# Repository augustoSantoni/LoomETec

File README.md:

# 🧶 LOOM ETEC - Telar Automático con Sistema Jacquard

## 📖 Descripción del Proyecto

El proyecto **LOOM ETEC** se desarrolla en el marco del taller **AeroGlobETec**, que combina disciplinas como ciencias, electrónica, informática, mecánica y dibujo técnico.

### 🎯 Motivación

Este proyecto nace de una motivación personal, inspirada en la memoria de mi abuela, quien dedicó gran parte de su vida a tejer y donar sus creaciones a quienes más lo necesitaban. Tras su fallecimiento, surgió la idea de conmemorar su legado mediante la creación de un telar automático que perpetúe su espíritu altruista e integre conocimientos técnicos.

**Objetivo principal**: Automatizar el proceso de tejido para producir mantas destinadas a instituciones que asisten a recién nacidos en situación de vulnerabilidad.

### 🏗️ Tipos de Telares Implementados

#### 1️⃣ Telar Convencional

Compuesto por cuatro partes esenciales:

- **Caladores**: Varillas que levantan o bajan selectivamente los hilos de la urdimbre, creando una abertura (llamada "calada") por donde pasa la lanzadera con el hilo de la trama.
- **Peine**: Herramienta dentada que presiona y compacta el hilo de la trama después de cada pasada de la lanzadera.
- **Lanzadera**: Dispositivo que transporta el hilo de la trama a través de los hilos de la urdimbre para tejer la tela.
- **Plegador**: Mecanismo que enrolla la tela tejida, manteniendo la tensión y avanzando la urdimbre a medida que se teje.

#### 2️⃣ Telar Jacquard (31 columnas)

Una reversión del telar de Jacquard, máquina textil que utiliza patrones digitales (en lugar de tarjetas perforadas) para controlar automáticamente el levantamiento individual de hilos de urdimbre, permitiendo la creación de patrones complejos.

**Sistema de control**:
- **Eje X**: Motor PAP para movimiento horizontal (31 posiciones)
- **Eje Z**: Servomotor para selección arriba/abajo de cada hilo
- **Eje Y**: Motor DC para elevación del cabezal (calada)

---

## 🛠️ Tecnologías Utilizadas

### Software

#### **PlatformIO**
IDE profesional para desarrollo de sistemas embebidos. Proporciona gestión de bibliotecas, compilación cruzada y soporte para múltiples plataformas de hardware. Utilizado para programar el ESP32 con C++.

#### **Node-RED**
Herramienta de programación visual basada en flujos para conectar dispositivos IoT. Actúa como middleware entre la interfaz web y el broker MQTT, procesando las peticiones HTTP y transformándolas en comandos MQTT.

#### **MQTT (Mosquitto/HiveMQ Cloud)**
Protocolo de mensajería ligero para IoT. Permite la comunicación asíncrona entre el ESP32 y el servidor mediante topics (tópicos). Se puede usar Mosquitto localmente o HiveMQ Cloud para acceso remoto.

#### **Autodesk Fusion 360**
Software de modelado 3D CAD/CAM utilizado para diseñar las piezas mecánicas del telar, incluyendo soportes, engranajes y estructuras.

#### **Python 3.x + Tkinter**
Lenguaje de programación utilizado para desarrollar el **Editor de Trama**, una aplicación de escritorio que permite crear patrones de tejido de forma visual mediante una interfaz gráfica.

### Hardware

| Componente | Descripción | Cantidad |
|------------|-------------|----------|
| **ESP32 DevKit V1** | Microcontrolador principal con WiFi y Bluetooth integrado | 1 |
| **Motores DC** | Para lanzadera, peine y eje Y (elevación) | 3-4 |
| **Servomotores** | Para selección de hilos (Eje Z) en sistema Jacquard | 1 |
| **Motores PAP + DVR8825** | Motor paso a paso con driver para eje X (horizontal) y plegador | 2 |
| **Puente H L298N** | Controlador para motores DC bidireccionales | 2-3 |
| **Sensores Fin de Carrera** | Detección de posiciones límite (mínimo 7) | 7+ |
| **Fuente de Alimentación** | 12V 5A para motores | 1 |
| **Cables y Conectores** | Jumpers, borneras, conectores Dupont | Varios |

---

## 📋 Requisitos Previos

### Software a Instalar

1. **Visual Studio Code** con extensión **PlatformIO IDE**
2. **Node.js** (v14 o superior) para Node-RED
3. **Python 3.8+** para el Editor de Trama
4. **Mosquitto MQTT Broker** (opcional, para pruebas locales)

---

## 🚀 Guía de Instalación

### 1. Instalación de PlatformIO

1. Descargar e instalar [Visual Studio Code](https://code.visualstudio.com/)
2. Abrir VS Code y dirigirse a **Extensions** (Ctrl+Shift+X)
3. Buscar **PlatformIO IDE** e instalar
4. Reiniciar VS Code
5. Verificar instalación: debería aparecer un ícono de hormiga en la barra lateral

### 2. Instalación de Node-RED

```bash
# Instalar Node.js desde https://nodejs.org/

# Instalar Node-RED globalmente
npm install -g node-red

# Instalar nodos adicionales necesarios
cd ~/.node-red
npm install node-red-dashboard
npm install node-red-contrib-mqtt-broker

# Iniciar Node-RED
node-red

# Acceder a http://localhost:1880
```

### 3. Instalación de Python y Dependencias

```bash
# Verificar instalación de Python
python --version

# Instalar dependencias del Editor de Trama
pip install pillow
pip install tk

# En Linux/Mac, puede ser necesario instalar tkinter:
sudo apt-get install python3-tk  # Ubuntu/Debian
```

### 4. Configuración de MQTT Broker

#### Opción A: Mosquitto Local

```bash
# Windows: Descargar desde https://mosquitto.org/download/
# Linux:
sudo apt-get install mosquitto mosquitto-clients

# Iniciar servicio
sudo systemctl start mosquitto
sudo systemctl enable mosquitto

# Verificar que está corriendo en puerto 1883
netstat -tuln | grep 1883
```

#### Opción B: HiveMQ Cloud (Recomendado para acceso remoto)

1. Crear cuenta gratuita en [HiveMQ Cloud](https://www.hivemq.com/mqtt-cloud-broker/)
2. Crear un nuevo cluster
3. Anotar credenciales (URL, puerto, usuario, contraseña)
4. Actualizar configuración en `main.cpp` y flujos de Node-RED

---

## 🎨 Editor de Trama - Guía de Uso

### Iniciar el Editor

```bash
python Editor-Trama.py
```

### Funcionalidades Principales

#### 1. Crear un Patrón

- **Tamaño**: El editor trabaja con una cuadrícula de 24x24 píxeles por defecto
- **Colores**: 
  - Negro (patrón activo)
  - Blanco (fondo)
- **Pintar**: Click izquierdo para pintar, click derecho para borrar

#### 2. Pinceles Disponibles

| Pincel | Descripción |
|--------|-------------|
| Punto | Pinta un solo píxel |
| Línea H | Línea horizontal de 3 píxeles |
| Línea V | Línea vertical de 3 píxeles |
| Cruz | Forma de cruz (5 píxeles) |
| Cuadrado | Cuadrado de 2x2 |
| Diagonal | Diagonal de 3x3 |

**Crear pincel personalizado**:
1. Click en "Crear Pincel"
2. Definir dimensiones (ej: 3x3)
3. Click en "Generar Cuadrícula"
4. Pintar el patrón deseado
5. "Guardar Pincel" → ingresar nombre → guardar archivo `.brush`

#### 3. Ajustar Tamaño del Lienzo

- **Agrandar**: Ctrl/Cmd + `+` o botón "Agrandar" (incrementa 4 filas)
- **Achicar**: Ctrl/Cmd + `-` o botón "Achicar" (reduce 4 filas, mínimo 24)

#### 4. Replicar Diseño

1. Crear un patrón base en las primeras 24 filas
2. Ingresar número de repeticiones (ej: 3)
3. Click en "Aplicar Replicación"
4. El patrón se repetirá verticalmente

#### 5. Exportar Patrón

##### Guardar como PNG (Ctrl/Cmd + S)
- Genera imagen con franjas de sincronización (patrón ajedrezado)
- Formato: 1 píxel = 1 hilo
- Incluye franjas cada 4 filas/columnas para alineación

##### Guardar como JSON (Ctrl/Cmd + J)
```json
{
  "dimensiones": [31, 100],
  "datos": [
    [0, 1, 0, 1, ...],
    [1, 0, 1, 0, ...],
    ...
  ]
}
```
- **IMPORTANTE**: Para el telar Jacquard, el patrón debe tener exactamente **31 columnas**
- 0 = hilo abajo (blanco), 1 = hilo arriba (negro)

#### 6. Atajos de Teclado

| Atajo | Acción |
|-------|--------|
| Ctrl/Cmd + Z | Deshacer |
| Ctrl/Cmd + Y | Rehacer |
| Ctrl/Cmd + L | Limpiar lienzo |
| Ctrl/Cmd + S | Guardar PNG |
| Ctrl/Cmd + J | Guardar JSON |
| Ctrl/Cmd + `+` | Agrandar lienzo |
| Ctrl/Cmd + `-` | Achicar lienzo |

---

## ⚡ Puesta en Marcha del Telar

### Paso 1: Conexiones del ESP32

#### Telar Convencional

```
LANZADERA:
  enaLanzadera → GPIO 29 (PWM)
  lanzadera1 → GPIO 28 (dirección 1)
  lanzadera2 → GPIO 20 (dirección 2)
  fdcLanzadera1 → GPIO 40 (fin de carrera izq)
  fdcLanzadera2 → GPIO 15 (fin de carrera der)

CALADORES:
  enaCaladores → GPIO 34 (PWM)
  caladores1 → GPIO 35 (subir)
  caladores2 → GPIO 27 (bajar)
  fdcCaladores → GPIO 16 (fin de carrera)

PEINE:
  enaPeine → GPIO 22 (PWM)
  peine1 → GPIO 24 (adelante)
  peine2 → GPIO 23 (atrás)
  fdcPeine1 → GPIO 13 (fin de carrera adelante)
  fdcPeine2 → GPIO 14 (fin de carrera atrás)

PLEGADOR:
  stepPlegador → GPIO 8 (pulsos)
  dirPlegador → GPIO 18 (dirección)
```

#### Telar Jacquard (adicional al convencional)

```
EJE X (Motor PAP):
  stepEjeX → GPIO 25
  dirEjeX → GPIO 26
  fdcEjeX_Home → GPIO 17 (posición inicial)

EJE Z (Servo):
  servoEjeZ → GPIO 19

EJE Y (Motor DC elevación):
  enaEjeY → GPIO 34 (PWM)
  ejeY_Up → GPIO 35
  ejeY_Down → GPIO 27
  fdcEjeY_Arriba → GPIO 16
  fdcEjeY_Abajo → GPIO 21
```

#### Diagrama de Conexión Puente H (ejemplo L298N)

```
ESP32           L298N          Motor DC
GPIO XX   →     ENA      →     (PWM control velocidad)
GPIO YY   →     IN1      →     (dirección)
GPIO ZZ   →     IN2      →     (dirección)
              OUT1/OUT2  →     Motor
GND       →     GND
12V       →     12V (fuente externa)
```

#### Conexión DVR8825 (Motor PAP)

```
ESP32           DVR8825        Motor PAP
GPIO XX   →     STEP
GPIO YY   →     DIR
             →  ENABLE (a GND o control)
12V fuente →    VMOT
GND        →    GND
             →  A1, A2, B1, B2 → Bobinas del motor
```

### Paso 2: Programar el ESP32

```bash
# Clonar el repositorio
git clone https://github.com/tu-usuario/loom-etec.git
cd loom-etec

# Abrir el proyecto en VS Code con PlatformIO
code .

# Configurar WiFi y MQTT en main.cpp (líneas 50-54)
String ssid = "TU_WIFI";
String password = "TU_PASSWORD";
const char* mqtt_server = "TU_BROKER_IP";  # localhost o IP de HiveMQ
const char* mqtt_user = "usuario";
const char* mqtt_pass = "contraseña";

# Compilar y subir (en VS Code)
# Click en el ícono "→" (PlatformIO: Upload) en la barra inferior
# O usar el atajo: Ctrl+Alt+U

# Monitorear salida serial
# Click en el ícono de enchufe (PlatformIO: Serial Monitor)
# O atajo: Ctrl+Alt+S
```

### Paso 3: Configurar Node-RED

```bash
# Iniciar Node-RED
node-red

# Abrir navegador en http://localhost:1880
```

#### Importar Flujo

1. Click en menú hamburguesa (☰) → **Import**
2. Seleccionar archivo:
   - `node-red-flujo-telar.json` (telar Jacquard con carga de patrón)
   - O `node-red-flujo-telar-simple.json` (telar convencional)
3. Click en **Import**

#### Configurar Broker MQTT en Node-RED

1. Doble click en cualquier nodo MQTT (ej: "mqtt_empezar")
2. Click en el lápiz junto a "Server"
3. Configurar:
   ```
   Server: localhost  (o IP del broker)
   Port: 1883
   Username: tu_usuario
   Password: tu_contraseña
   ```
4. Click en **Update** → **Done**
5. Click en **Deploy** (botón rojo arriba a la derecha)

#### Verificar Endpoints HTTP

Una vez desplegado, los siguientes endpoints estarán disponibles:

```
POST http://localhost:1880/api/empezar       - Iniciar tejido
POST http://localhost:1880/api/parar         - Detener tejido
POST http://localhost:1880/api/config/red    - Configurar WiFi
POST http://localhost:1880/api/config/patron - Cargar patrón JSON (solo Jacquard)
GET  http://localhost:1880/api/vueltas       - Obtener contador de vueltas
```

### Paso 4: Interfaz Web

#### Opción 1: Servidor Local Simple

```bash
# Navegar a la carpeta del proyecto
cd loom-etec

# Iniciar servidor HTTP simple con Python
python -m http.server 8000

# Abrir navegador en:
http://localhost:8000/index.html
```

#### Opción 2: Servidor Web Externo

Subir el archivo `index.html` a cualquier hosting web o usar:

```bash
# Con Node.js (live-server)
npm install -g live-server
live-server --port=8000
```

### Paso 5: Operación del Sistema

#### Para Telar Convencional

1. Verificar que el ESP32 esté conectado a WiFi (revisar Serial Monitor)
2. Abrir interfaz web en `http://localhost:8000/index.html`
3. Verificar conexión:
   - Debe mostrar vueltas: 0
   - Botones deben estar habilitados
4. Click en **▶ Iniciar** para comenzar tejido
5. El telar ejecutará la secuencia automáticamente
6. Click en **■ Detener** para pausar

#### Para Telar Jacquard

1. Crear patrón en Editor de Trama (31 columnas)
2. Exportar como JSON (Ctrl+J)
3. Abrir interfaz web
4. En "Cargar patrón":
   - Click en zona de arrastre o seleccionar archivo
   - Elegir el archivo `.json` generado
   - Click en **Subir patrón al telar**
   - Esperar confirmación "🟢 Patrón subido correctamente"
5. Click en **▶ Iniciar**
6. El telar ejecutará el patrón columna por columna

---

## 🔧 Calibración y Ajustes

### Calibración del Sistema Jacquard

En `main.cpp`, ajustar las siguientes constantes según tu hardware:

```cpp
// Línea 60-65
#define PASOS_POR_COLUMNA 200    // Ajustar según distancia entre columnas
#define DELAY_PASO_X 800         // Velocidad del motor PAP (microsegundos)
#define SERVO_POS_ABAJO 45       // Posición servo para dejar hilo abajo
#define SERVO_POS_ARRIBA 135     // Posición servo para fijar hilo arriba
#define SERVO_DELAY 150          // Tiempo de movimiento del servo
```

### Ajuste de Velocidades de Motores

```cpp
// Línea 115-120
ledcWrite(PWM_LANZADERA, 200);  // 0-255: ajustar velocidad lanzadera
ledcWrite(PWM_PEINE, 200);      // 0-255: ajustar velocidad peine
ledcWrite(PWM_EJE_Y, 200);      // 0-255: ajustar velocidad elevación
```

### Tiempos de Estabilización

```cpp
// Línea 70-75
#define DELAY_TEJER 500           // Pausa entre ciclos completos
#define TIEMPO_ESTABILIDAD 200    // Pausa tras cada movimiento
#define TIEMPO_ESPERA_FDC 15000   // Timeout para sensores de fin de carrera
```

---

## 📡 Arquitectura del Sistema

```
┌─────────────────┐
│  Interfaz Web   │ ← Usuario interactúa
│  (index.html)   │
└────────┬────────┘
         │ HTTP (fetch)
         ▼
┌─────────────────┐
│   Node-RED      │ ← Middleware (localhost:1880)
│  (flujo.json)   │
└────────┬────────┘
         │ MQTT
         ▼
┌─────────────────┐
│ Broker MQTT     │ ← Mosquitto/HiveMQ
│  (puerto 1883)  │
└────────┬────────┘
         │ WiFi
         ▼
┌─────────────────┐
│     ESP32       │ ← Control de hardware
│   (main.cpp)    │
└────────┬────────┘
         │ GPIO
         ▼
┌─────────────────┐
│ Motores/Sensores│ ← Sistema mecánico
└─────────────────┘
```

---

## 🐛 Solución de Problemas

### ESP32 no se conecta a WiFi

```cpp
// Verificar credenciales en main.cpp
String ssid = "NOMBRE_EXACTO";  // Sin espacios extra
String password = "PASSWORD_EXACTA";

// Verificar en Serial Monitor:
// - "Conectando a SSID..."
// - "WiFi conectado"
// - "IP: xxx.xxx.xxx.xxx"
```

### Node-RED no recibe mensajes MQTT

1. Verificar broker MQTT está corriendo:
   ```bash
   sudo systemctl status mosquitto
   # o
   mosquitto -v
   ```

2. Probar conexión con mosquitto_sub:
   ```bash
   mosquitto_sub -h localhost -t "empezar" -v
   ```

3. Verificar configuración de broker en Node-RED coincide con ESP32

### Sensores de fin de carrera no funcionan

```cpp
// Verificar lógica de activación (línea 30)
#define FDC_PRESIONADO LOW  // Cambiar a HIGH si usa pull-down

// Agregar resistencias pull-up/down según tipo de sensor
```

### Servo no se mueve correctamente

```cpp
// Calibrar posiciones del servo (línea 62-63)
#define SERVO_POS_ABAJO 45      // Probar valores entre 0-180
#define SERVO_POS_ARRIBA 135    // Ajustar según rango del servo

// Verificar alimentación del servo (5V, GND correcto)
```

### Motor PAP pierde pasos

```cpp
// Aumentar delay entre pasos (línea 61)
#define DELAY_PASO_X 1200  // Valor más alto = movimiento más lento pero preciso

// Verificar:
// - Conexión de bobinas del motor
// - Configuración de micropasos en DVR8825
// - Alimentación suficiente (12V)
```

---

## 📊 Tópicos MQTT

### Publicados por ESP32

| Tópico | Payload | Descripción |
|--------|---------|-------------|
| `vuelta` | Número entero | Contador de vueltas completadas |

### Suscritos por ESP32

| Tópico | Payload | Descripción |
|--------|---------|-------------|
| `empezar` | `"1"` | Iniciar tejido |
| `parar` | `"1"` | Detener tejido |
| `config/red` | JSON: `{"ssid": "...", "password": "..."}` | Configurar WiFi |
| `config/patron` | JSON: `{"filename": "...", "content": "{...}"}` | Cargar patrón (Jacquard) |

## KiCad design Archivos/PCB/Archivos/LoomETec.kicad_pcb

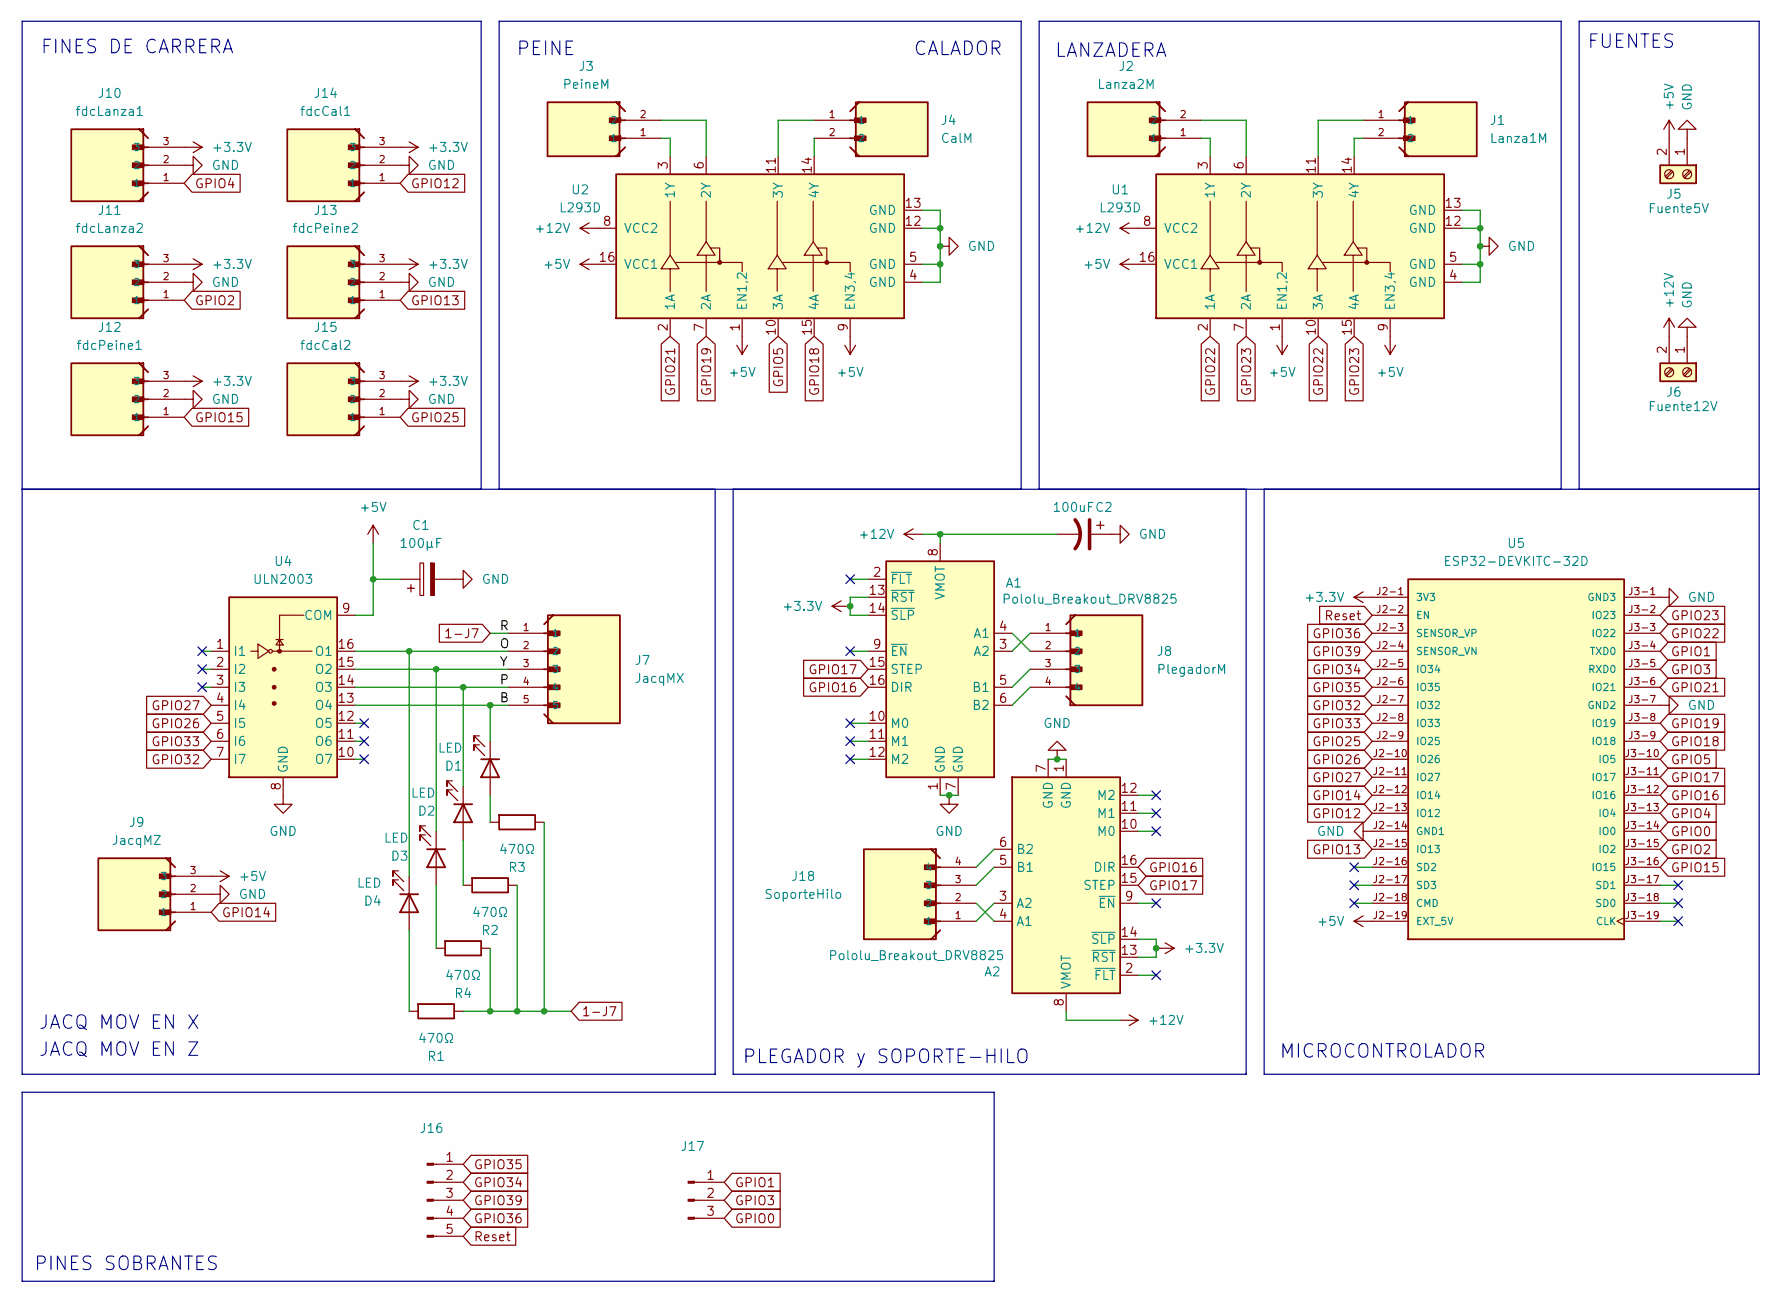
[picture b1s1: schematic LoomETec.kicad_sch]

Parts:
A1, A2: Pololu_Breakout_DRV8825; DRV8825-PT
C1: 100µF; CP_Radial_D6.3mm_P2.50mm
C2: 100uF; CP_Radial_D6.3mm_P2.50mm
D1, D2, D3, D4: LED; LED_D5.0mm
J1: Lanza1M; JST_XH_B2B-XH-A_1x02_P2.50mm_Vertical
J2: Lanza2M; JST_XH_B2B-XH-A_1x02_P2.50mm_Vertical
J3: PeineM; JST_XH_B2B-XH-A_1x02_P2.50mm_Vertical
J4: CalM; JST_XH_B2B-XH-A_1x02_P2.50mm_Vertical
J5: Fuente5V; TerminalBlock_MaiXu_MX126-5.0-02P_1x02_P5.00mm
J6: Fuente12V; TerminalBlock_MaiXu_MX126-5.0-02P_1x02_P5.00mm
J7: JacqMX; JST_XH_B5B-XH-A_1x05_P2.50mm_Vertical
J8: PlegadorM; JST_XH_B4B-XH-A_1x04_P2.50mm_Vertical
J9: JacqMZ; JST_XH_B3B-XH-A_1x03_P2.50mm_Vertical
J10: fdcLanza1; JST_XH_B3B-XH-A_1x03_P2.50mm_Vertical
J11: fdcLanza2; JST_XH_B3B-XH-A_1x03_P2.50mm_Vertical
J12: fdcPeine1; JST_XH_B3B-XH-A_1x03_P2.50mm_Vertical
J13: fdcPeine2; JST_XH_B3B-XH-A_1x03_P2.50mm_Vertical
J14: fdcCal1; JST_XH_B3B-XH-A_1x03_P2.50mm_Vertical
J15: fdcCal2; JST_XH_B3B-XH-A_1x03_P2.50mm_Vertical
J16: Conn_01x05_Pin; PinHeader_1x05_P2.54mm_Vertical
J17: Conn_01x03_Pin; PinHeader_1x03_P2.54mm_Vertical
J18: SoporteHilo; JST_XH_B4B-XH-A_1x04_P2.50mm_Vertical
R1, R2, R3, R4: 470Ω; R_Axial_DIN0207_L6.3mm_D2.5mm_P10.16mm_Horizontal
U1, U2: L293D; DIP-16_W7.62mm
U4: ULN2003; DIP794W45P254L1969H508Q16
U5: ESP32-DEVKITC-32D; NODEMCU-ESP-32S; PARTREV V4

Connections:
1-J7: J7.1, R1.1, R2.1, R3.1, R4.1
+3.3V: A1.13 (~RST), A1.14 (~SLP), A2.13 (~RST), A2.14 (~SLP), J10.3, J11.3, J12.3, J13.3, J14.3, J15.3, U5.J2-1 (3V3)
+5V: C1.1, J5.2, J9.3, U1.1 (EN1,2), U1.9 (EN3,4), U1.16 (VCC1), U2.1 (EN1,2), U2.9 (EN3,4), U2.16 (VCC1), U4.9 (COM), U5.J2-19 (EXT_5V)
+12V: A1.8 (VMOT), A2.8 (VMOT), C2.2, J6.2, U1.8 (VCC2), U2.8 (VCC2)
/B: D1.1 (K), J7.5, U4.13 (O4)
/O: D4.1 (K), J7.2, U4.16 (O1)
/P: D2.1 (K), J7.4, U4.14 (O3)
/Y: D3.1 (K), J7.3, U4.15 (O2)
GND: A1.1 (GND), A1.7 (GND), A2.1 (GND), A2.7 (GND), C1.2, C2.1, J5.1, J6.1, J9.2, J10.2, J11.2, J12.2, J13.2, J14.2, J15.2, U1.4 (GND), U1.5 (GND), U1.12 (GND), U1.13 (GND), U2.4 (GND), U2.5 (GND), U2.12 (GND), U2.13 (GND), U4.8 (GND), U5.J2-14 (GND1), U5.J3-1 (GND3), U5.J3-7 (GND2)
GPIO0: J17.3, U5.J3-14 (IO0)
GPIO1: J17.1, U5.J3-4 (TXD0)
GPIO2: J11.1, U5.J3-15 (IO2)
GPIO3: J17.2, U5.J3-5 (RXD0)
GPIO4: J10.1, U5.J3-13 (IO4)
GPIO5: U2.10 (3A), U5.J3-10 (IO5)
GPIO12: J14.1, U5.J2-13 (IO12)
GPIO13: J13.1, U5.J2-15 (IO13)
GPIO14: J9.1, U5.J2-12 (IO14)
GPIO15: J12.1, U5.J3-16 (IO15)
GPIO16: A1.16 (DIR), A2.16 (DIR), U5.J3-12 (IO16)
GPIO17: A1.15 (STEP), A2.15 (STEP), U5.J3-11 (IO17)
GPIO18: U2.15 (4A), U5.J3-9 (IO18)
GPIO19: U2.7 (2A), U5.J3-8 (IO19)
GPIO21: U2.2 (1A), U5.J3-6 (IO21)
GPIO22: U1.2 (1A), U1.10 (3A), U5.J3-3 (IO22)
GPIO23: U1.7 (2A), U1.15 (4A), U5.J3-2 (IO23)
GPIO25: J15.1, U5.J2-9 (IO25)
GPIO26: U4.5 (I5), U5.J2-10 (IO26)
GPIO27: U4.4 (I4), U5.J2-11 (IO27)
GPIO32: U4.7 (I7), U5.J2-7 (IO32)
GPIO33: U4.6 (I6), U5.J2-8 (IO33)
GPIO34: J16.2, U5.J2-5 (IO34)
GPIO35: J16.1, U5.J2-6 (IO35)
GPIO36: J16.4, U5.J2-3 (SENSOR_VP)
GPIO39: J16.3, U5.J2-4 (SENSOR_VN)
unnamed: A1.4 (A1), J8.2
unnamed: A1.3 (A2), J8.1
unnamed: A1.5 (B1), J8.3
unnamed: A1.6 (B2), J8.4
unnamed: A2.4 (A1), J18.2
unnamed: A2.3 (A2), J18.1
unnamed: A2.5 (B1), J18.3
unnamed: A2.6 (B2), J18.4
unnamed: D1.2 (A), R3.2
unnamed: D2.2 (A), R2.2
unnamed: D3.2 (A), R4.2
unnamed: D4.2 (A), R1.2
unnamed: J2.1, U1.3 (1Y)
unnamed: J2.2, U1.6 (2Y)
unnamed: J1.1, U1.11 (3Y)
unnamed: J1.2, U1.14 (4Y)
unnamed: J3.1, U2.3 (1Y)
unnamed: J3.2, U2.6 (2Y)
unnamed: J4.1, U2.11 (3Y)
unnamed: J4.2, U2.14 (4Y)
Reset: J16.5, U5.J2-2 (EN)

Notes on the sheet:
LANZADERA
FUENTES
JACQ MOV EN X
PLEGADOR y SOPORTE-HILO
CALADOR
PINES SOBRANTES
FINES DE CARRERA
MICROCONTROLADOR
JACQ MOV EN Z
PEINE

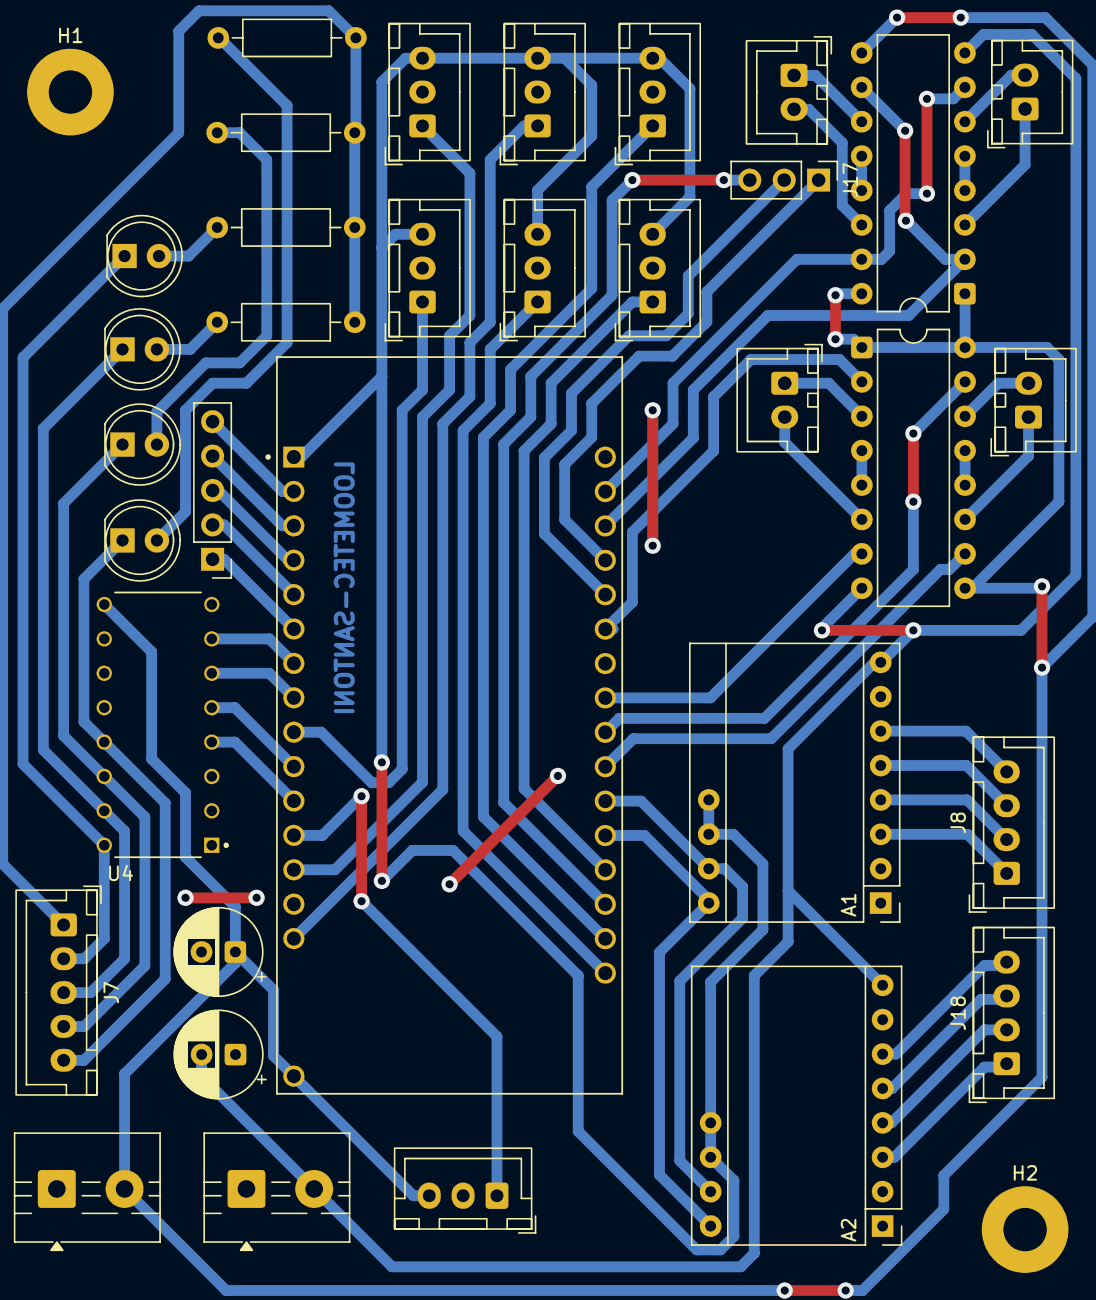
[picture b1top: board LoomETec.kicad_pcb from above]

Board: 2 copper layers, 36 parts (0 on the bottom side), 56 nets.

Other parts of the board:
H1, H2: MountingHole_3.2mm_M3_Pad

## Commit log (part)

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2026-01-18 Remove large video file
2026-01-18 Add .gitignore for video files
2026-01-18 Add README and gitignore, remove large video
2026-01-18 Refactor README for clarity and conciseness
    Removed motivation section and future improvements from README. Updated installation instructions and fixed formatting for code blocks.
2026-01-24 Revise README for LOOM ETEC project
    Updated README with project details, installation instructions, and system architecture.

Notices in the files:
README.md:
License: MIT
